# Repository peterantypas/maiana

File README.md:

# MAIANA&trade;: The Open Source AIS Transponder

I started this project around 2015 with the intention of experimenting and eventually building something for my own boat.
I was not impressed with commercial AIS class B transponders. They seemed bloated, expensive and some of them were particularly power-hungry. Also, my boat is rather small and I have very little room for "nav" instruments, so I didn't want a huge enclosure inside plus two external RF cables, one for VHF and one for GPS. So I set out to create my own "lean and mean" design and I sailed with it for 2 years.

Fast forward to 2023, and it has taken a life of its own:

The main difference between MAIANA&trade; and every commercial transponder is that it's a self-contained unit, and thus its performance is 100% repeatable. The entire transponder circuit, the GNSS and all antennas are in the same housing. The design has been validated by fabricating _over 300 units_ now (July 2023).

So with all the core functionality kept outside and under tight control, the only other thing we need is power and data connections. Now, what's the most common cable that can carry a few signals 50 feet away? If you guessed "Ethernet", you guessed right. Commonplace Cat5 cable can deliver power plus serial data signals anywhere on an average sized pleasure boat. So that's how the exterior unit connects to the cabin, where one of these breakouts offers USB, NMEA0183 or NMEA2000 adapters to connect to the rest of the boat's systems. 

## Hardware Design

### Mechanical
The antenna casing that you see in these photos is a piece of 1" Schedule 40 "furniture" grade PVC pipe. It is the highest grade of such material, with a solid white PVC core (not a coated household grade pipe). Still, it's the most inexpensive UV resistant material available, and it looks great too!

The VHF antenna whip is built using an epoxy wound filament tube coated with high quality, UV resistant irradiated polyolefin ("heat shrink"). The company that makes this tubing (and helped me with this design challenge) also built the landing gear for NASA's Ingenuity helicopter on Mars, so they definitely understand how to deal with harsh environments. The bottomline is that unlike typical fiberglass antenna masts, this antenna is not going to degrade and "blossom" under continuous UV exposure. Starting with January of 2022, the antenna tube will be made of two telescopic pieces of the same material. This will greatly reduce the cost of shipping the kit to Europe and Australia.

The entire outdoor assembly is held together by the same high grade heat shrink tubing, so there is no need for any adhesives! The main water seal is formed by heat shrinking around a specially designed 3D printed cap made of PLA. This part naturally softens when heated and as it's compressed by the heat shrink tubing surrounding it, it forms a permanent, watertight colar around the antenna tube. This blocks rain water and salt spray from the top. A layer of clear heat shrink in the interior forms a secondary water seal encompassing the lower part of the antenna. Finally, the PCB can be sprayed with conformal coating for an added layer of protection. Silicone spray works best and has no appreciable detuning effect on the GNSS.

With no adhesives getting in the way, the unit can actually be opened and serviced by (carefully) cutting through the heat shrink tubing with a knife, then resealing with the same material and method as before. This, in fact, was one of my design goals from the beginning.

### Electrical
As I mentioned already, the transponder circuit is inside the antenna case. It's a 24mm x 84mm 4-layer PCB:

The core design is based on two Silicon Labs "EZRadio Pro" series ICs. All kits shipping today are based on the Si4460.

The microcontroller on this board is a STM32L4 series (422, 431 and 432 supported). I chose these because the 80MHz clock allows the SPI bus to operate at exactly 10MHz which is the maximum supported by the Si446x ICs. This is important, as a transponder is a *hard real time* application, so SPI latency must be minimized. All kits today are based on the STM32L432KBU6.

The GNSS is now a Quectel L76L-M33 and relies on a Johansson ceramic chip antenna. It usually takes a minute to acquire a fix outdoors from a cold start. With the latest antenna tuning, it offers near-navigation grade accuracy (typical HDOP at sea is less than 2 meters).

The transmitter front end is based on a power MOSFET typically found in handheld VHF radios and outputs just over 2 Watts (+33dBm). It has a verified range of over 20 nautical miles on a masthead and 10+ miles on a pushpit.

The system is designed to run from a 12V battery and exposes a 3.3V-level UART for connecting to the rest of the boat. The UART continuously sends GPS and AIS data in NMEA0183 format at 38.4Kbps. It also accepts certain commands for management. The breakout boxes pictured above deliver this stream via USB, NME0183 (RS422) or NMEA 2000 (CAN). The 3 "fancy" breakouts feature _galvanic isolation_ of their USB connection to avoid causing unintended problems with laptops and other devices whose power supplies are meant to _float_. This also means that you cannot use USB to power MAIANA&trade; - it must connect to a 12V battery.

In addition, there is now a "bare bones" UART+USB breakout:

This provides the simplest, lowest cost interface to a Raspberry Pi, Arduino or any other similar system you may want to wire directly. It is _not_ galvanically isolated to keep the cost really low. This adapter is now part of the base kit and ships with every configuration.

For the circuit to transmit, it must be configured with persistent station data (MMSI, call sign, name, dimensions, etc). This is stored in an EEPROM and is provisioned over a USB/serial connection via a command line interface. If station data is not provisioned, the device will simply run as a 2 channel AIS + GNSS receiver.

SOTDMA synchronization is based on the very acurate 1 PPS signal from the GNSS and the UTC clock. MAIANA&trade; does not synchronize itself to other stations because practical experience revealed that it's literally the "Wild West" out there: There are *many* commercial class A systems in operation today with buggy time slot management, so the simplest solution is to not rely on any of them. That said, the design behaves as a "class B" so it will not attempt to reserve time slots. It will just transmit autonomously and independently, based on Clear Channel Assessment, at the schedule permitted for this class of device. 

All adapters (except the "bare bones" one) feature a *silent mode* switch to explicitly disable transmission. If you need this for the UART adapter, you can wire one yourself.

In terms of power consumption, the main board draws about 45mA from 12V in receive mode, and spikes up to 700mA during transmission (for only 27 milliseconds). The adapters add an extra 0.5mA - 25mA depending on choice. So MAIANA&trade;'s most power hungry configuration needs about 0.6 Watts, which is a lot less than a typical LED-based cabin light.

### Software

The transponder firmware is an [Eclipse CDT project](latest/Firmware/Transponder) that you could clone and build. The code is C++ with a BSP abstraction layer so you need to tweak bsp/bsp.hpp or define one of the required symbols in the preprocessor to build for different board revisions. It contains snippets of STM32Cube generated code, but is does not follow ST's "spaghetti" structure.

The NMEA2000 adapter also has its own separate [firmware project](latest/Firmware/NMEA2000Adapter).

As of December 2021, MAIANA&trade; is fully integrated into [OpenPlotter](https://openmarine.net/openplotter). This means that it can be provisioned and managed entirely from its graphical interface, including firmware updates. To accomplish this, I had to make both a hardware and a software change: 

- The hardware change was to reinstate the I2C EEPROM that I used in earlier designs. This was necessary because STM32 applications that are interrupt heavy cannot safely erase and write any pages in the same flash bank, as the *entire* bank gets locked. This means that the next interrupt may be unable to execute, thus causing the processor to hang until the watchdog resets it. Moving persistence to an EEPROM solves this problem.

- The software change was to dust off the original [bootloader](latest/Firmware/Bootloader) that I wrote years ago and make it bulletproof: Even if you manage to brick the unit by uploading garbage firmware into it, it has a built-in "rescue" mode. All you have to do is toggle the TX switch a couple of times during the first 2 seconds after power-up and it will enter firmware update mode again.

### CAD

Everything is [here](latest/CAD). 

### Building the unit

This is going to be difficult for all but the most technically advanced. The board features all surface mounted components, with 4 QFNs, a few SOT-363s and tightly spaced 0603 passives. The antenna switch on board 11.3.0 is about 0.8 x 1 mm and you'll need a microscope to align it. So unless you're very skilled and well equipped, you will find it difficult to build. 

### Buying a kit

I have developed a kit which includes pre-soldered (and programmed) boards as well as the antenna, main casing and heat shrink tubing. See [the installation manual here](https://github.com/peterantypas/maiana/blob/master/latest/Manuals/MAIANA%E2%84%A2%20Assembly%20Manual%20(Rev%204).pdf) to get a better idea of the process.

If you are located in North America, send an email to *maiana.kits@_dontspam_gmail.com* (remove the spambot blocker of course). Tariffs have made it difficult to ship to Europe and vice versa, so [OpenMarine](https://shop.openmarine.net) is working with European based teams to build and ship directly from Barcelona, Spain.

### License

CAD and transponder firmware are licensed under GPLV3. I chose the most "copyleft" license to discourage commercial entities from ripping this off and then "close-sourcing" it. The flipside of this is that if you can fork the design and make something better, then you deserve the success! That said, MAIANA&trade; will become a registered trademark soon, so if you plan to do this you must use a different name.

The NMEA2000 adapter firmware is under MIT license to be consistent with the libraries it depends on. Feel free to use it as you wish.

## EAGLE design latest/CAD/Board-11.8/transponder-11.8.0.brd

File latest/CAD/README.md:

## Board design files

This directory contains Eagle CAD files as well as schematic PDFs and Gerber exports for board fabrication.

The board stackup is good enough for either OSH Park 4-layer, or JLCPCB 4-layer with controlled impedance (JLC2313). 

### Latest Board

Revision 11.5.2 does away with the (hard to source) regulator from ST and replaces it with a Zener + NPN combination that delivers about 8.5V to the PA under load.

### Breakouts
These directories contain Eagle and FreeCAD files for the NMEA0183, NMEA 2000 and USB adapters. Their front panels are PCBs so gerbers are
here as well. The UART+USB adapter is a very basic breakout board for those who would rather wire the transponder themselves.

### Antenna
This directory contains FreeCAD and STEP exports of the 3D printed parts that make up the antenna.

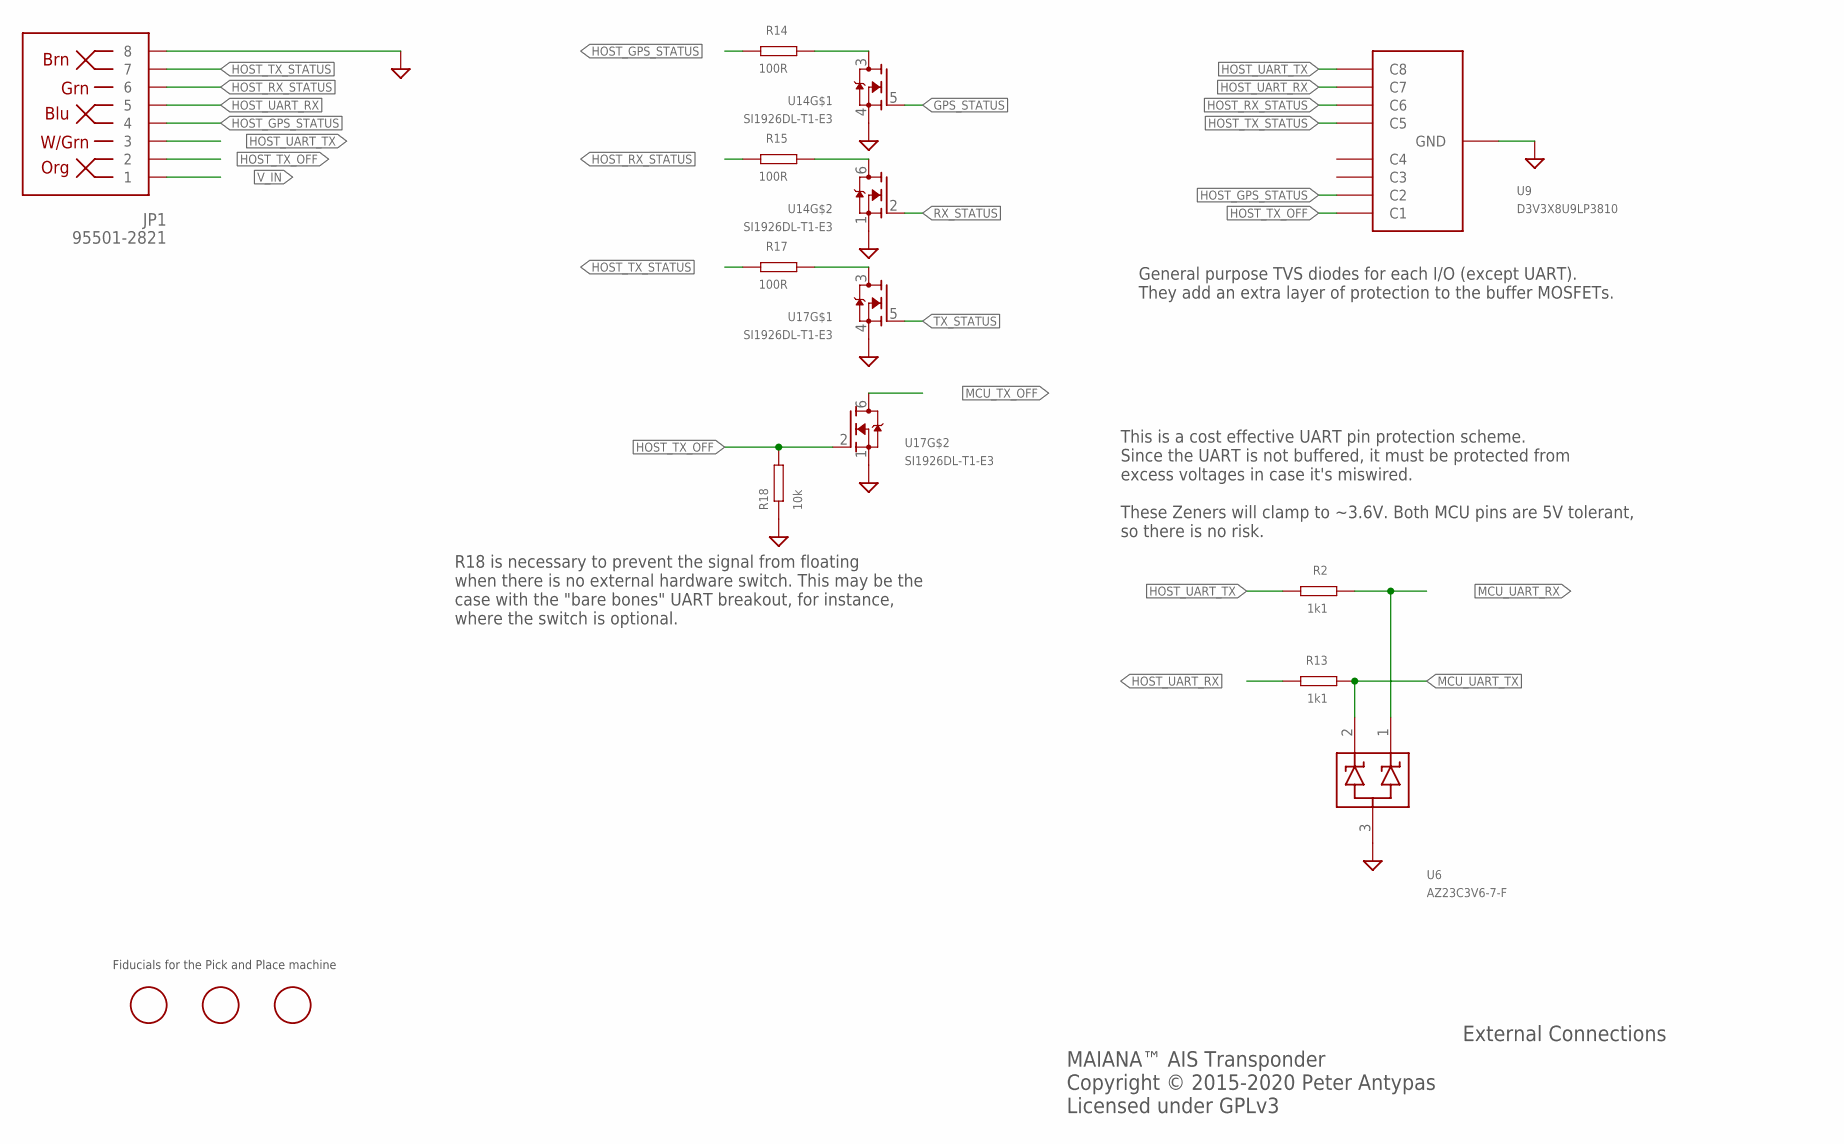
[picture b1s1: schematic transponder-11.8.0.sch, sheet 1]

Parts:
JP1: 95501-2821; RJ45-8; PARTNO 95501-2821
R2, R13: 1k1; 0603; PARTNO CR0603JA0112G
R14, R15, R17: 100R; 0603; PARTNO RMC1/16K101FTP
R18: 10k; 0603; PARTNO CR0603JA0103G
U6: AZ23C3V6-7-F; SOT-23; PARTNO AZ23C3V6-7-F
U9: D3V3X8U9LP3810; U-DFN3810-9(B)
U14, U17: SI1926DL-T1-E3; SOT363; PARTNO SI1926DL-T1-E3
U$1, U$2, U$3: FIDUCIAL; FIDUCIAL_1MM

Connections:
GND: JP1.8, R18.P$1, U6.3, U9.P$3 (GND), U14.1 (S), U14.4 (S), U17.1 (S), U17.4 (S); also elsewhere on the board
GPS_STATUS: U14.5 (G); also elsewhere on the board
HOST_GPS_STATUS: JP1.4, R14.P$2, U9.P$2 (C2)
HOST_RX_STATUS: JP1.6, R15.P$2, U9.P$7 (C6)
HOST_TX_OFF: JP1.2, R18.P$2, U9.P$1 (C1), U17.2 (G)
HOST_TX_STATUS: JP1.7, R17.P$2, U9.P$6 (C5)
HOST_UART_RX: JP1.5, R13.P$2, U9.P$8 (C7)
HOST_UART_TX: JP1.3, R2.P$2, U9.P$9 (C8)
MCU_TX_OFF: U17.6 (D); also elsewhere on the board
MCU_UART_RX: R2.P$1, U6.1; also elsewhere on the board
MCU_UART_TX: R13.P$1, U6.2; also elsewhere on the board
unnamed: R14.P$1, U14.3 (D)
unnamed: R15.P$1, U14.6 (D)
unnamed: R17.P$1, U17.3 (D)
RX_STATUS: U14.2 (G); also elsewhere on the board
TX_STATUS: U17.5 (G); also elsewhere on the board
V_IN: JP1.1; also elsewhere on the board

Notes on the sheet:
External Connections
MAIANA™ AIS Transponder Copyright © 2015-2020 Peter Antypas Licensed under GPLv3
Fiducials for the Pick and Place machine
R18 is necessary to prevent the signal from floating when there is no external hardware switch. This may be the case with the "bare bones" UART breakout, for instance, where the switch is optional.
This is a cost effective UART pin protection scheme. Since the UART is not buffered, it must be protected from excess voltages in case it's miswired. These Zeners will clamp to ~3.6V. Both MCU pins are 5V tolerant, so there is no risk.
General purpose TVS diodes for each I/O (except UART). They add an extra layer of protection to the buffer MOSFETs.

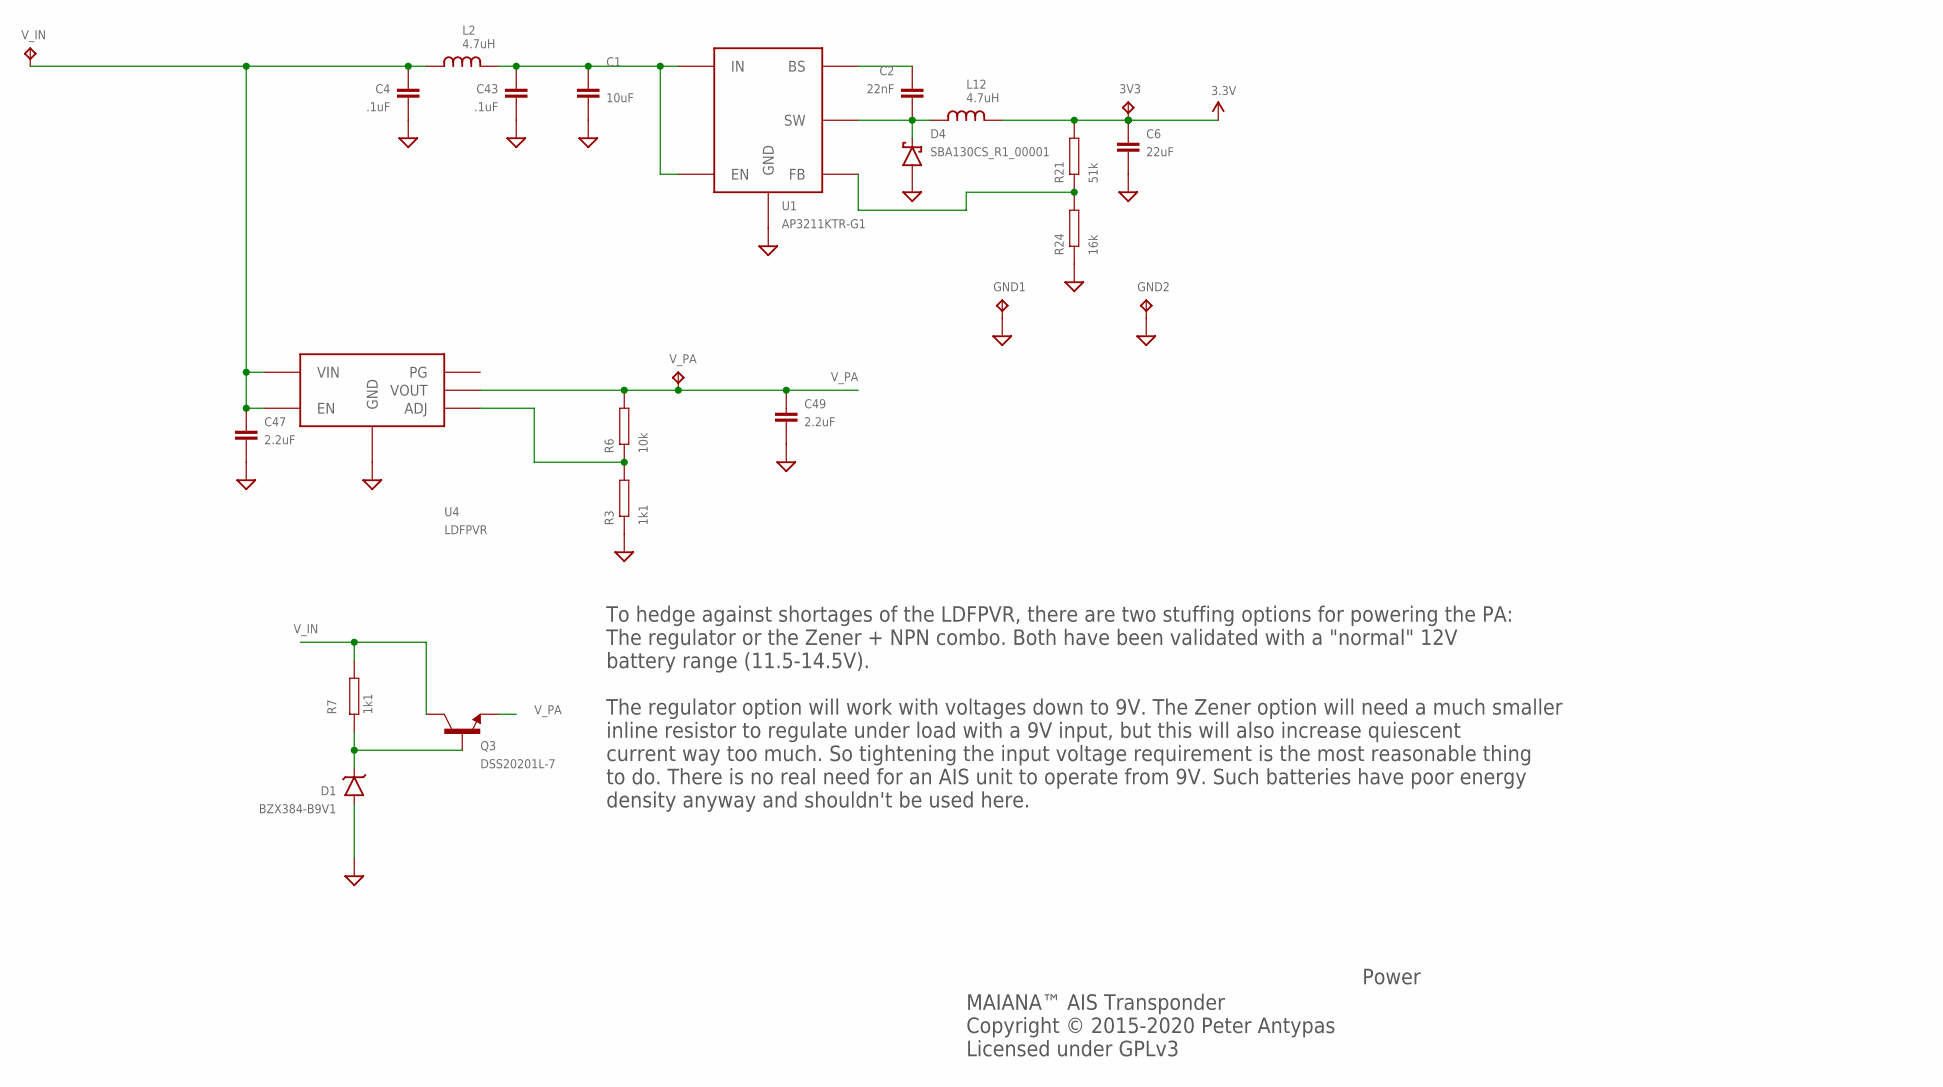
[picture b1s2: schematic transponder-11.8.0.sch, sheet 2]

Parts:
3V3: TPTP12R; TP12R
C1: 10uF; 0805; PARTNO EMK212ABJ106KG-T
C2: 22nF; 0603; PARTNO CL10B223KA8NNNC
C4, C43: .1uF; 0603; PARTNO 0603B104K250CT
C6: 22uF; 0805; PARTNO CL21A226KOQNNNE
C47, C49: 2.2uF; 0603; PARTNO 0603X225K160CT
D1: BZX384-B9V1; SOD323; PARTNO BZX384-B9V1
D4: SBA130CS_R1_00001; SOD323; PARTNO SBA130CS_R1_00001
GND1, GND2: TPTP12R; TP12R
L2, L12: 4.7uH; 0805; PARTNO CMP201209UD4R7MT
Q3: DSS20201L-7; SOT23-3; PARTNO DSS20201L-7
R3, R7: 1k1; 0603; PARTNO CR0603JA0112G
R6: 10k; 0603; PARTNO CR0603JA0103G
R21: 51k; 0603; PARTNO CR0603FA5102G
R24: 16k; 0603; PARTNO RC0603FR-0716KL
U1: AP3211KTR-G1; SOT23-6; PARTNO AP3211KTR-G1
U4: LDFPVR; DFN6-2X2
V_IN: TPTP12R; TP12R
V_PA: TPTP12R; TP12R

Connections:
3.3V: 3V3.TP, C6.P$1 (1), L12.P$2 (2), R21.P$2; also elsewhere on the board
GND: C1.P$2 (2), C4.P$2 (2), C6.P$2 (2), C43.P$2 (2), C47.P$2 (2), C49.P$2 (2), D1.A, D4.A, GND1.TP, GND2.TP, R3.P$1, R24.P$1, U1.2 (GND), U4.P$4 (GND), U4.P$7 (GND); also elsewhere on the board
unnamed: C2.P$2 (2), D4.C, L12.P$1 (1), U1.6 (SW)
unnamed: D1.C, Q3.1 (B), R7.P$1
unnamed: C2.P$1 (1), U1.1 (BS)
unnamed: R21.P$1, R24.P$2, U1.3 (FB)
unnamed: C1.P$1 (1), C43.P$1 (1), L2.P$2 (2), U1.4 (EN), U1.5 (IN)
unnamed: R3.P$2, R6.P$1, U4.P$2 (ADJ)
V_IN: C4.P$1 (1), C47.P$1 (1), L2.P$1 (1), Q3.3 (C), R7.P$2, U4.P$5 (EN), U4.P$6 (VIN), V_IN.TP; also elsewhere on the board
V_PA: C49.P$1 (1), Q3.2 (E), R6.P$2, U4.P$1 (VOUT), V_PA.TP; also elsewhere on the board

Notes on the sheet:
MAIANA™ AIS Transponder Copyright © 2015-2020 Peter Antypas Licensed under GPLv3
Power
To hedge against shortages of the LDFPVR, there are two stuffing options for powering the PA: The regulator or the Zener + NPN combo. Both have been validated with a "normal" 12V battery range (11.5-14.5V). The regulator option will work with voltages down to 9V. The Zener option will need a much s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

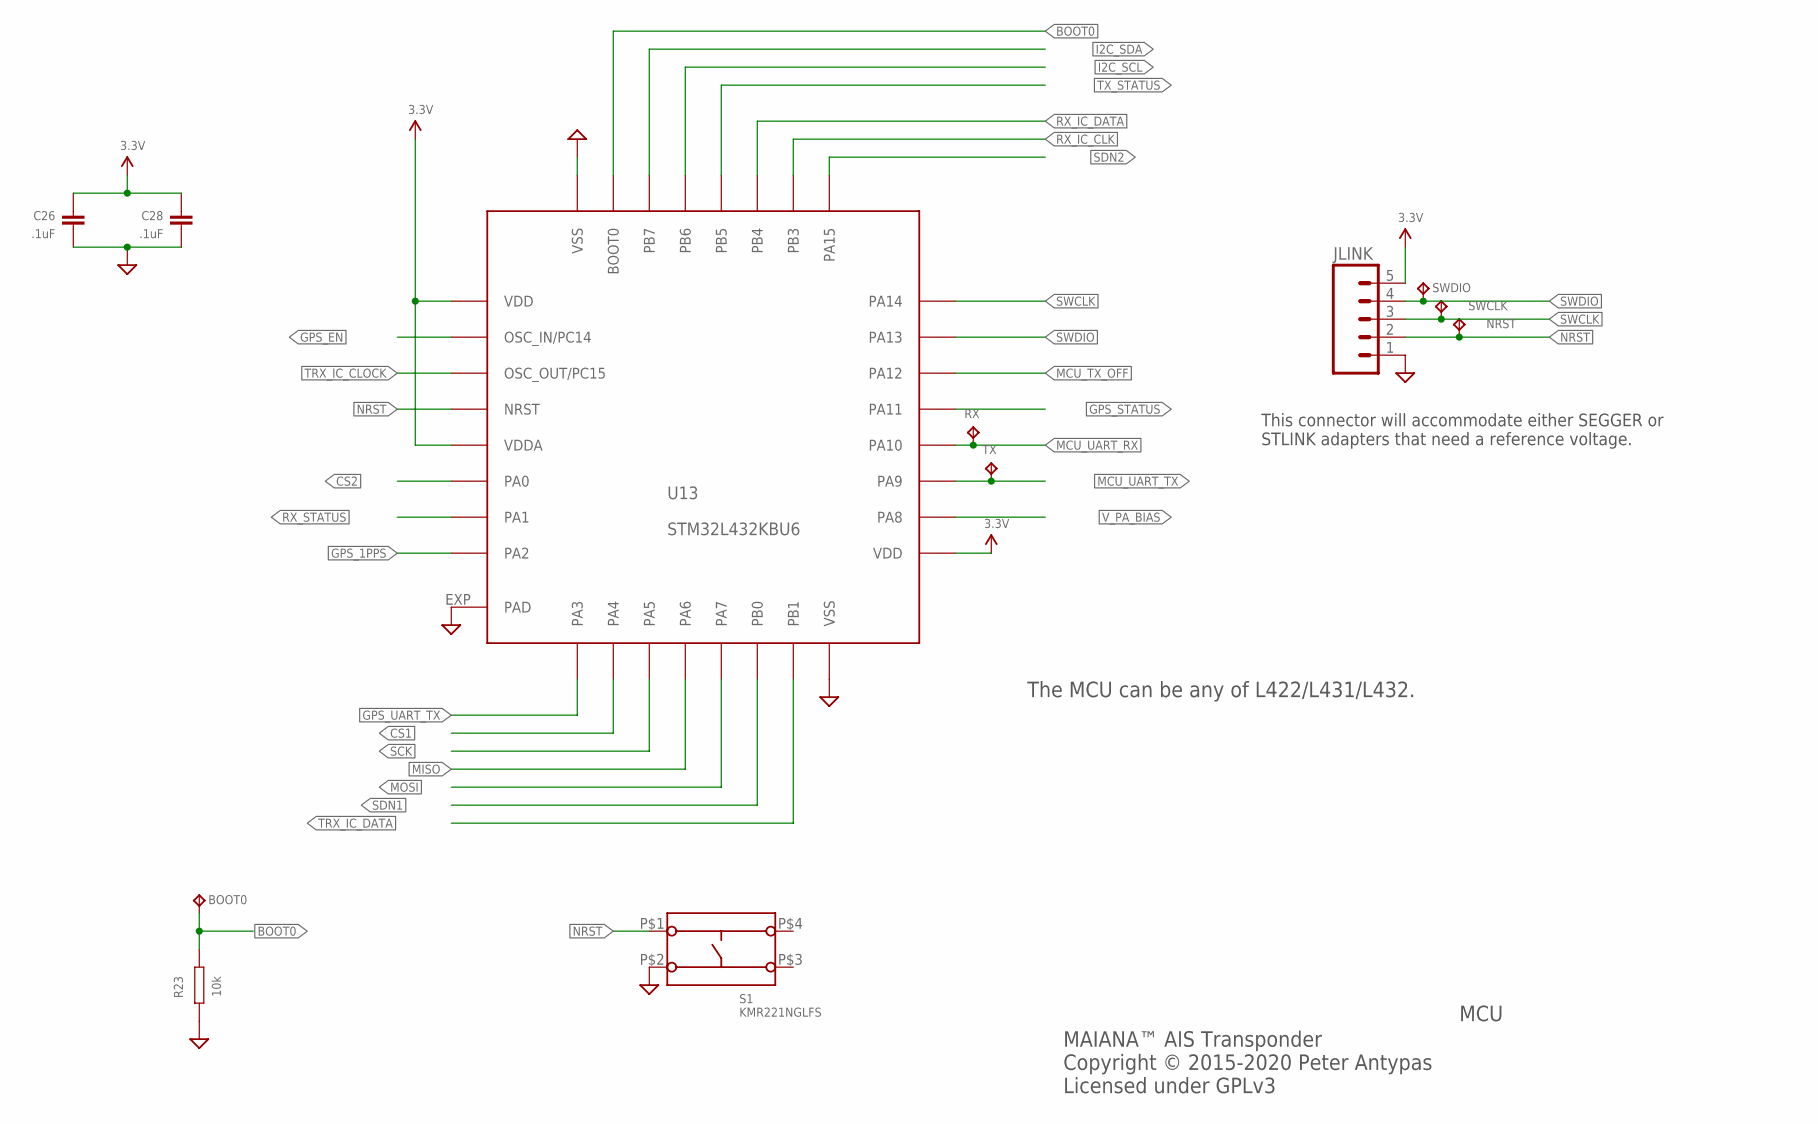
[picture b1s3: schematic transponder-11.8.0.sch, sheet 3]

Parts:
BOOT0: TPTP12R; TP12R
C26, C28: .1uF; 0603; PARTNO 0603B104K250CT
JLINK: M05PTH; 1X05
NRST: TPTP12R; TP12R
R23: 10k; 0603; PARTNO CR0603JA0103G
RX: TPTP12R; TP12R
S1: KMR221NGLFS
SWCLK: TPTP12R; TP12R
SWDIO: TPTP12R; TP12R
TX: TPTP12R; TP12R
U13: STM32L432KBU6; QFN32; PARTNO STM32L432KBU6

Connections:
3.3V: C26.P$1 (1), C28.P$1 (1), JLINK.5, U13.1 (VDD), U13.5 (VDDA), U13.17 (VDD); also elsewhere on the board
BOOT0: BOOT0.TP, R23.P$1, U13.31 (BOOT0)
CS1: U13.10 (PA4); also elsewhere on the board
CS2: U13.6 (PA0); also elsewhere on the board
GND: C26.P$2 (2), C28.P$2 (2), JLINK.1, R23.P$2, S1.P$2 (S2), U13.16 (VSS), U13.32 (VSS), U13.EXP (PAD); also elsewhere on the board
GPS_1PPS: U13.8 (PA2); also elsewhere on the board
GPS_EN: U13.2 (OSC_IN/PC14); also elsewhere on the board
GPS_STATUS: U13.21 (PA11); also elsewhere on the board
GPS_UART_TX: U13.9 (PA3); also elsewhere on the board
I2C_SCL: U13.29 (PB6); also elsewhere on the board
I2C_SDA: U13.30 (PB7); also elsewhere on the board
MCU_TX_OFF: U13.22 (PA12); also elsewhere on the board
MCU_UART_RX: RX.TP, U13.20 (PA10); also elsewhere on the board
MCU_UART_TX: TX.TP, U13.19 (PA9); also elsewhere on the board
MISO: U13.12 (PA6); also elsewhere on the board
MOSI: U13.13 (PA7); also elsewhere on the board
NRST: JLINK.2, NRST.TP, S1.P$1 (S1), U13.4 (NRST)
RX_IC_CLK: U13.26 (PB3); also elsewhere on the board
RX_IC_DATA: U13.27 (PB4); also elsewhere on the board
RX_STATUS: U13.7 (PA1); also elsewhere on the board
SCK: U13.11 (PA5); also elsewhere on the board
SDN1: U13.14 (PB0); also elsewhere on the board
SDN2: U13.25 (PA15); also elsewhere on the board
SWCLK: JLINK.3, SWCLK.TP, U13.24 (PA14)
SWDIO: JLINK.4, SWDIO.TP, U13.23 (PA13)
TRX_IC_CLOCK: U13.3 (OSC_OUT/PC15); also elsewhere on the board
TRX_IC_DATA: U13.15 (PB1); also elsewhere on the board
TX_STATUS: U13.28 (PB5); also elsewhere on the board
V_PA_BIAS: U13.18 (PA8); also elsewhere on the board

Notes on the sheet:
MCU
MAIANA™ AIS Transponder Copyright © 2015-2020 Peter Antypas Licensed under GPLv3
The MCU can be any of L422/L431/L432.
This connector will accommodate either SEGGER or STLINK adapters that need a reference voltage.

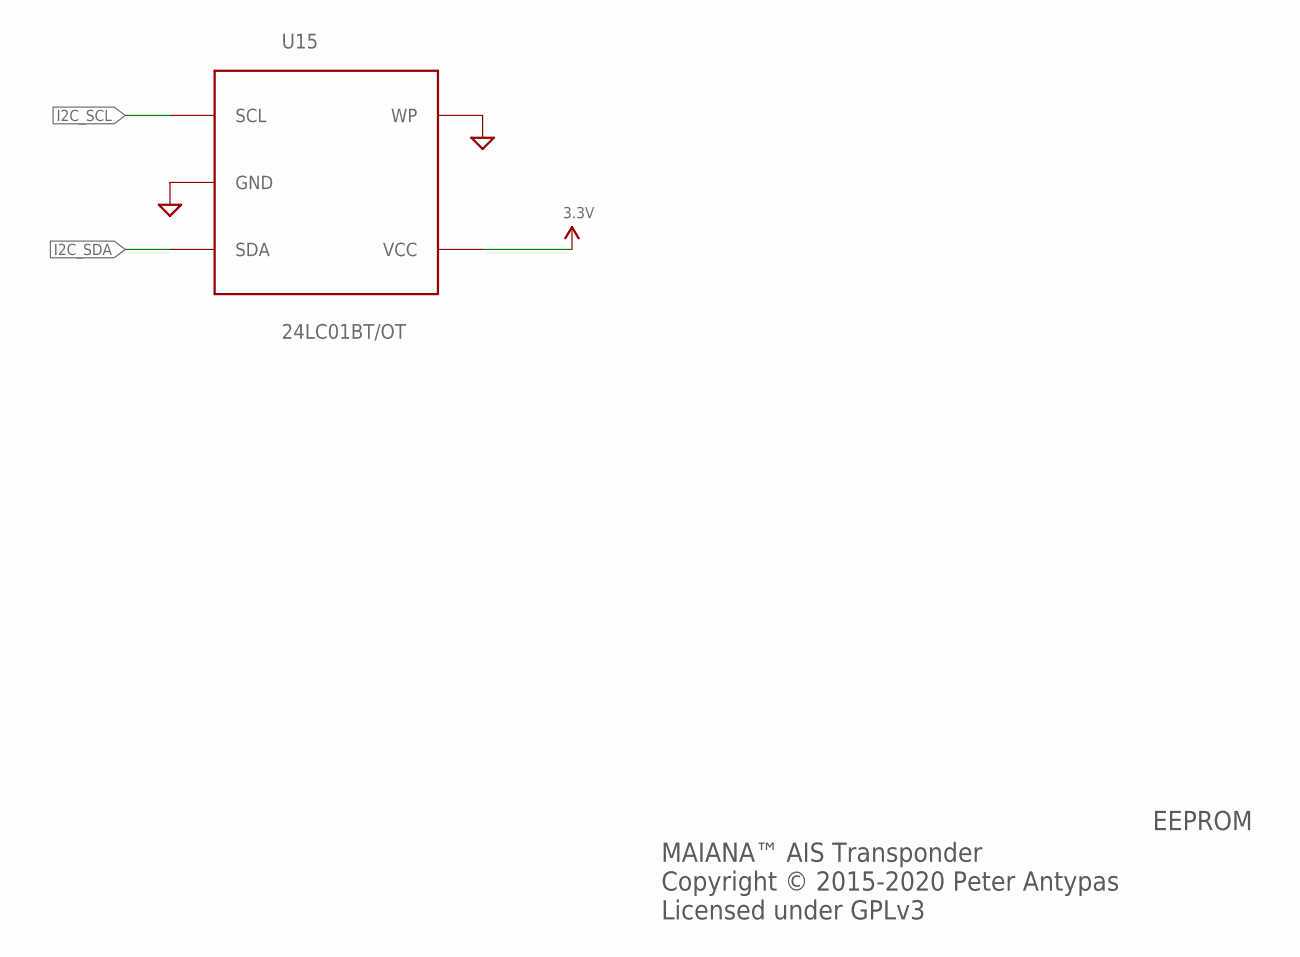
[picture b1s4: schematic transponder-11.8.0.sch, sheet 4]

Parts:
U15: 24LC01BT/OT; SOT23-5; PARTNO 24LC01BT/OT

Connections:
3.3V: U15.4 (VCC); also elsewhere on the board
GND: U15.2 (GND), U15.5 (WP); also elsewhere on the board
I2C_SCL: U15.1 (SCL); also elsewhere on the board
I2C_SDA: U15.3 (SDA); also elsewhere on the board

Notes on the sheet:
EEPROM
MAIANA™ AIS Transponder Copyright © 2015-2020 Peter Antypas Licensed under GPLv3

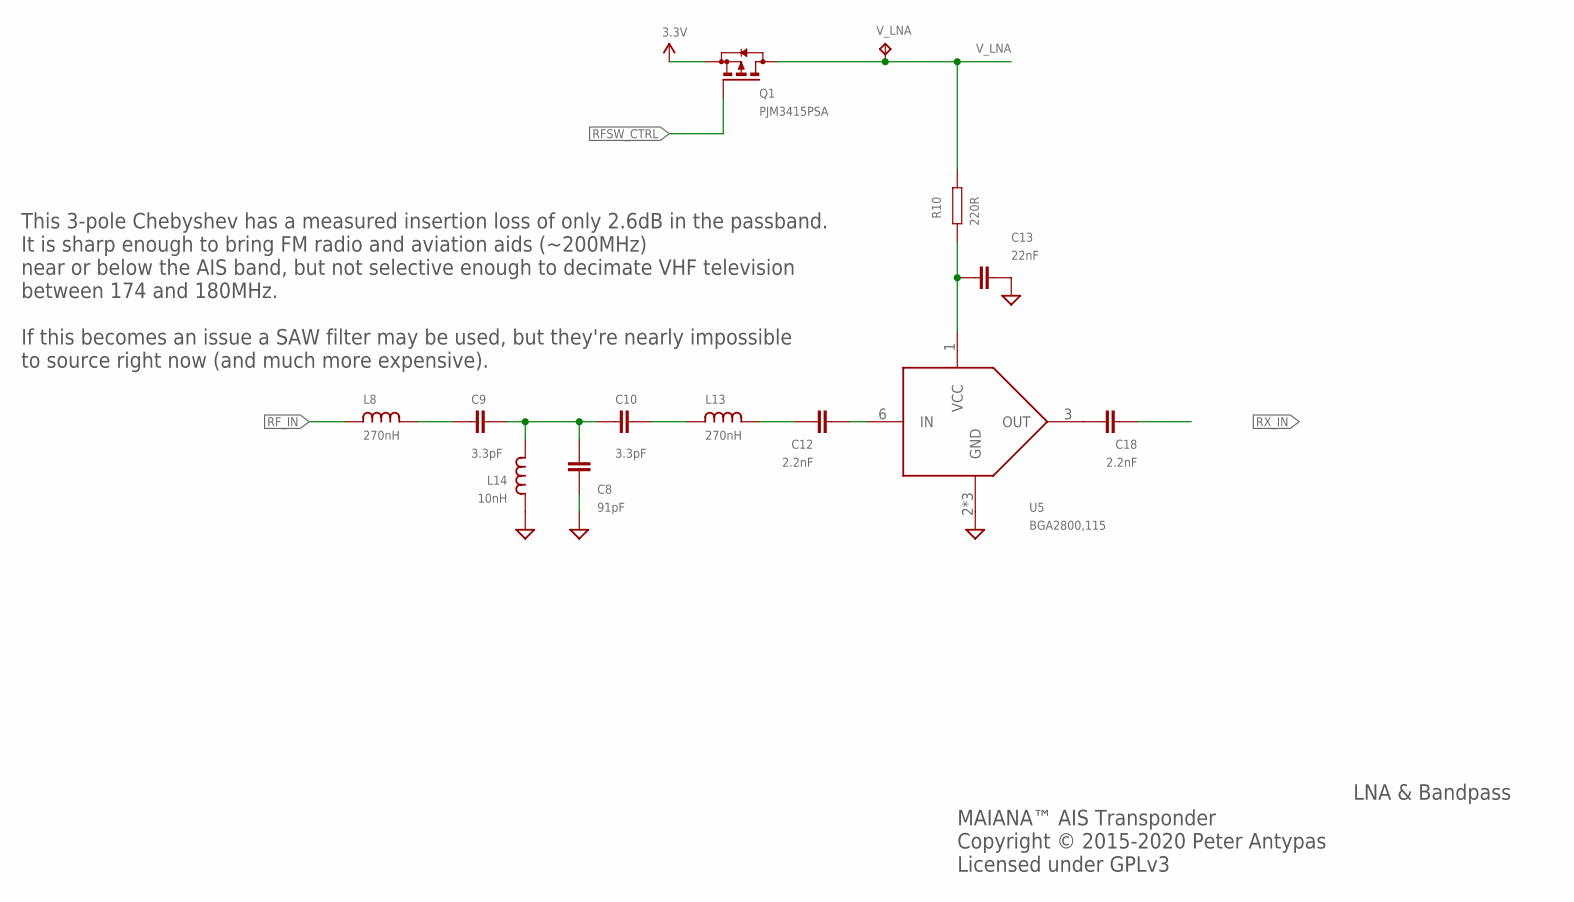
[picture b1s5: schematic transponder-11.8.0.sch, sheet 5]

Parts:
C8: 91pF; 0603; PARTNO CC0603JRNPO9BN910
C9, C10: 3.3pF; 0603; PARTNO 0603N3R3B500CT
C12, C18: 2.2nF; 0603; PARTNO 0603N222J500CT
C13: 22nF; 0603; PARTNO CL10B223KA8NNNC
L8, L13: 270nH; 0603; PARTNO LQW18ANR27G00D
L14: 10nH; 0603; PARTNO LQW18AN10NG00D
Q1: PJM3415PSA; SOT23; PARTNO PJM3415PSA
R10: 220R; 0603; PARTNO CR0603FA2200G
U5: BGA2800,115; SOT363; PARTNO BGA2800,115
V_LNA: TPTP12R; TP12R

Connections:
3.3V: Q1.2 (S); also elsewhere on the board
GND: C8.P$2 (2), C13.P$2 (2), L14.P$1 (1), U5.2 (GND), U5.4 (GND), U5.5 (GND); also elsewhere on the board
unnamed: C12.P$2 (2), U5.6 (IN)
unnamed: C9.P$1 (1), L8.P$2 (2)
unnamed: C8.P$1 (1), C9.P$2 (2), C10.P$1 (1), L14.P$2 (2)
unnamed: C10.P$2 (2), L13.P$1 (1)
unnamed: C12.P$1 (1), L13.P$2 (2)
unnamed: C13.P$1 (1), R10.P$2, U5.1 (VCC)
unnamed: C18.P$1 (1), U5.3 (OUT)
RFSW_CTRL: Q1.1 (G); also elsewhere on the board
RF_IN: L8.P$1 (1); also elsewhere on the board
RX_IN: C18.P$2 (2); also elsewhere on the board
V_LNA: Q1.3 (D), R10.P$1, V_LNA.TP; also elsewhere on the board

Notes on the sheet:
LNA & Bandpass
MAIANA™ AIS Transponder Copyright © 2015-2020 Peter Antypas Licensed under GPLv3
This 3-pole Chebyshev has a measured insertion loss of only 2.6dB in the passband. It is sharp enough to bring FM radio and aviation aids (~200MHz) near or below the AIS band, but not selective enough to decimate VHF television between 174 and 180MHz. If this becomes an issue a SAW filter may be us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

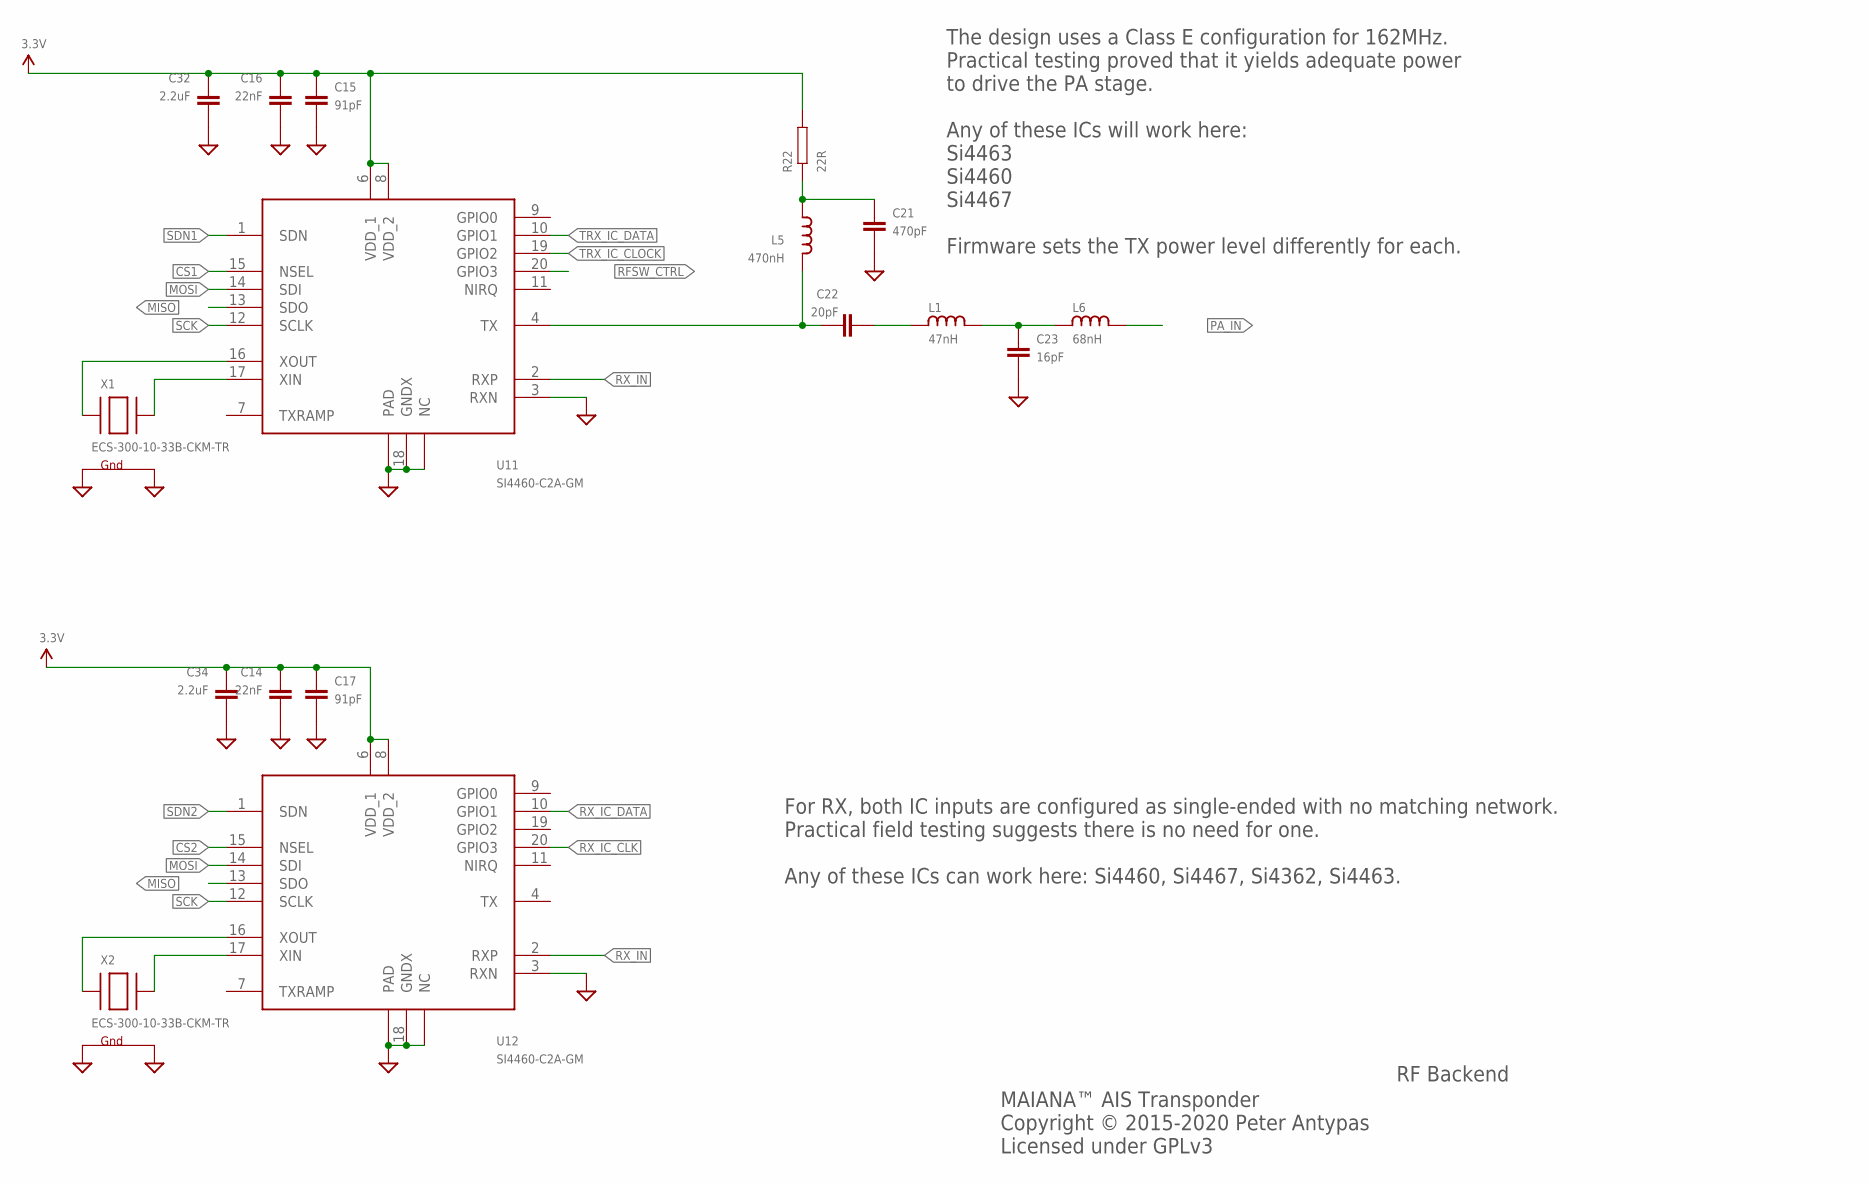
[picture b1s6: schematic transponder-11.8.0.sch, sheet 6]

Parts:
C14, C16: 22nF; 0603; PARTNO CL10B223KA8NNNC
C15, C17: 91pF; 0603; PARTNO CC0603JRNPO9BN910
C21: 470pF; 0603; PARTNO 0603B471K500CT
C22: 20pF; 0603; PARTNO CL10C200JB8NNNC
C23: 16pF; 0603; PARTNO 0603N160G500CT
C32, C34: 2.2uF; 0603; PARTNO 0603X225K160CT
L1: 47nH; 0603; PARTNO LQW18AN47NG00D
L5: 470nH; 0603; PARTNO HBLS1608-R47J
L6: 68nH; 0603; PARTNO LQW18AN68NG00D
R22: 22R; 0603; PARTNO RC0603JR-0722RL
U11, U12: SI4460-C2A-GM; QFN20; PARTNO SI4460-C2A-GM
X1, X2: ECS-300-10-33B-CKM-TR; NX3225; PARTNO ECS-300-10-33B-CKM-TR

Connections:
3.3V: C14.P$1 (1), C15.P$1 (1), C16.P$1 (1), C17.P$1 (1), C32.P$1 (1), C34.P$1 (1), R22.P$2, U11.6 (VDD_1), U11.8 (VDD_2), U12.6 (VDD_1), U12.8 (VDD_2); also elsewhere on the board
CS1: U11.15 (NSEL); also elsewhere on the board
CS2: U12.15 (NSEL); also elsewhere on the board
GND: C14.P$2 (2), C15.P$2 (2), C16.P$2 (2), C17.P$2 (2), C21.P$2 (2), C23.P$2 (2), C32.P$2 (2), C34.P$2 (2), U11.3 (RXN), U11.5 (NC), U11.18 (GNDX), U11.EXP (PAD), U12.3 (RXN), U12.5 (NC), U12.18 (GNDX), U12.EXP (PAD), X1.2 (G2), X1.4 (G1), X2.2 (G2), X2.4 (G1); also elsewhere on the board
MISO: U11.13 (SDO), U12.13 (SDO); also elsewhere on the board
MOSI: U11.14 (SDI), U12.14 (SDI); also elsewhere on the board
unnamed: C23.P$1 (1), L1.P$2 (2), L6.P$1 (1)
unnamed: U12.16 (XOUT), X2.1 (X1)
unnamed: U12.17 (XIN), X2.3 (X2)
unnamed: U11.16 (XOUT), X1.1 (X1)
unnamed: U11.17 (XIN), X1.3 (X2)
unnamed: C22.P$1 (1), L5.P$2 (2), U11.4 (TX)
unnamed: C21.P$1 (1), L5.P$1 (1), R22.P$1
unnamed: C22.P$2 (2), L1.P$1 (1)
PA_IN: L6.P$2 (2); also elsewhere on the board
RFSW_CTRL: U11.20 (GPIO3); also elsewhere on the board
RX_IC_CLK: U12.20 (GPIO3); also elsewhere on the board
RX_IC_DATA: U12.10 (GPIO1); also elsewhere on the board
RX_IN: U11.2 (RXP), U12.2 (RXP); also elsewhere on the board
SCK: U11.12 (SCLK), U12.12 (SCLK); also elsewhere on the board
SDN1: U11.1 (SDN); also elsewhere on the board
SDN2: U12.1 (SDN); also elsewhere on the board
TRX_IC_CLOCK: U11.19 (GPIO2); also elsewhere on the board
TRX_IC_DATA: U11.10 (GPIO1); also elsewhere on the board

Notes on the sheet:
RF Backend
MAIANA™ AIS Transponder Copyright © 2015-2020 Peter Antypas Licensed under GPLv3
The design uses a Class E configuration for 162MHz. Practical testing proved that it yields adequate power to drive the PA stage. Any of these ICs will work here: Si4463 Si4460 Si4467 Firmware sets the TX power level differently for each.
For RX, both IC inputs are configured as single-ended with no matching network. Practical field testing suggests there is no need for one. Any of these ICs can work here: Si4460, Si4467, Si4362, Si4463.

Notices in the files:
latest/CAD/NMEA0183Breakout/NMEA0183Breakout-3.0.brd:
(c)2021 P. Antypas
latest/CAD/UARTBreakout/UARTBreakout-3.0.brd:
(c)2021 Maverick Labs LLC
parts and their libraries:
SparkFun-Connectors: Licensing: Creative Commons ShareAlike 4.0 International - https://creativecommons.org/licenses/by-sa/4.0
COPYRIGHT: Copyright (C) 2018 Accelerated Designs. All rights reserved
